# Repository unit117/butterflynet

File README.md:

# KiCad Agent Pipeline

> A multi-agent workflow that operates KiCad end to end: research a physical product, review and normalize the spec, generate the board, repair design-rule failures, and export fabrication files.

This project was built for the GOSIM Paris 2026 Agentic AI Hackathon. The target is a recreation-inspired PCB for Ingo Maurer's **My New Flame** lamp: a tall, narrow 430x30mm board with two LED faces, a stem/base interface, and manufacturable KiCad outputs.

The key idea is not "LLM writes a PCB once." The system keeps an auditable chain of agents around KiCad: source-gathering, claim review, spec branching, deterministic board generation, DRC repair, and fabrication export. The demo UI replays the real agent logs and KiCad artifacts so judges can see where agents made decisions, caught mistakes, and recovered from failed fixes.

---

## Why This Matters

Hardware design is a good stress test for agentic AI because plausible text is not enough. A wrong charger IC, incorrect LED topology, or broken clearance rule becomes a real manufacturing problem. This project shows agents doing the work around the artifact:

- reading source material before creating a spec
- rejecting unsupported or electrically invalid claims
- refusing to build a blocked faithful reconstruction
- branching to a buildable modernized target
- generating KiCad schematic/PCB files
- running automated DRC loops until the board reaches zero violations
- exporting Gerbers, drill files, BOM, placement CSV, and a 3D model

The result is a working local demo plus a complete KiCad hardware project that reviewers can inspect directly.

---

## Demo Flow

Run the local replay UI and press **Play**. The app shows six screens: an overview, then the five pipeline phases.

| Phase | What reviewers see | Why it matters |
|---|---|---|
| 0. Overview | KiCad context and project goal | Frames the real EDA environment, not just a mock UI |
| 1. Research | Sources, facts, unresolved questions, source previews, terminal log | Shows source discipline before design work starts |
| 2. Design | Multi-agent review, rejected claims, branch selection | Shows self-correction and refusal to guess |
| 3. Build | KiCad component groups and generated board structure | Shows the system moving from spec to concrete PCB artifacts |
| 4. Validate | DRC loop, improvements, regressions, reverts, final zero-violation state | Shows agents reading tool feedback and recovering from failures |
| 5. Export | Fabrication bundle, individual files, spinning GLB board preview | Shows manufacturing-ready outputs |

The required 3-5 minute demo video is supplied through the hackathon submission. This repository contains the local demo used to produce that video.

---

## Judging Criteria Fit

**Innovation:** The project treats KiCad as an agent-operable engineering environment. Agents do not only draft text; they inspect evidence, branch specs, run tools, measure failures, and decide when not to proceed.

**Technical depth:** The repo includes a real KiCad 10 project, replay logs, a React/Vite provenance UI, custom KiCad automation scripts, DRC recovery outputs, fabrication files, and a 3D GLB preview.

**Completeness:** The demo covers the whole path from research to export. The hardware project includes `.kicad_pro`, `.kicad_sch`, `.kicad_pcb`, custom footprints, Gerbers, drill files, BOM, position CSV, PDFs, STEP/GLB, and DRC reports.

**Practicality:** The workflow targets a real engineering failure mode: AI systems that hallucinate hardware details and stop before validation. This pipeline makes uncertainty visible and closes the loop with KiCad checks.

**Presentation:** The UI is a deterministic replay of the pipeline, with phase-by-phase controls and visual artifacts for judges to follow in a 3 minute live demo.

---

## Agentic Moments

**Phase 2: self-correction**

- A reviewer agent rejects the proposed MCP73871 charger IC because it is a single-cell Li-Ion charger, while the original target uses 4x AA NiMH cells.
- A design-research agent corrects the claim that the LEDs are physically flame-shaped. Source evidence shows an 8x16 rectangular LED field per face; the flame is rendered by animation.
- The system refuses to build the faithful reconstruction while charger topology remains unresolved, then selects the `v5_modernized` branch as the build target.

**Phase 4: failure recovery**

- DRC starts at 451 violations and reaches 0 after 33 iterations.
- Some proposed fixes improve the board and are kept.
- Some fixes make the DRC count worse and are reverted.
- Later fixes can succeed after earlier routing context changes, showing that the validation loop is state-aware rather than a static checklist.

---

## Run Locally

Requirements:

- Node.js 20+
- npm
- A modern browser

Start the demo:

```bash
cd kicad-agent-ui/frontend
npm install
npm run dev
```

Open:

```text
http://localhost:5173/
```

Build the frontend:

```bash
cd kicad-agent-ui/frontend
npm run build
```

The frontend is self-contained for demo playback. KiCad is not required to run the replay UI, but the hardware files can be opened in KiCad 10 for inspection.

---

## Repository Map

```text
.
├── agents/                         # Agent role prompts and responsibilities
├── examples/                       # Example user prompts for faithful and modernized builds
├── hardware/
│   ├── README.md                   # Hardware artifact notes
│   ├── candle-git-history.bundle   # Preserved original candle project history
│   └── candle/                     # Full KiCad project and generated outputs
├── kicad-agent-ui/
│   ├── backend/                    # FastAPI skeleton for project/pipeline/viewer APIs
│   └── frontend/                   # React/Vite replay UI
├── replays/                        # Canonical NDJSON phase replay logs
├── DEMO.md                         # Demo/provenance notes
├── DISCLOSURE.md                   # Pre-existing vs hackathon-built disclosure
├── SUBMISSION.md                   # Hackathon metadata checklist
└── README.md
```

---

## Hardware Artifacts

The complete KiCad project is in [hardware/candle](hardware/candle).

Key source files:

- [hardware/candle/candle.kicad_pro](hardware/candle/candle.kicad_pro)
- [hardware/candle/candle.kicad_sch](hardware/candle/candle.kicad_sch)
- [hardware/candle/candle.kicad_pcb](hardware/candle/candle.kicad_pcb)
- [hardware/candle/candle.pretty](hardware/candle/candle.pretty)
- [hardware/candle/tools/generate_candle.py](hardware/candle/tools/generate_candle.py)
- [hardware/candle/tools/candle_recovery.py](hardware/candle/tools/candle_recovery.py)
- [hardware/candle/outputs/fabrication](hardware/candle/outputs/fabrication)
- [hardware/candle/outputs/candle.glb](hardware/candle/outputs/candle.glb)

The frontend also serves compact demo copies from:

- [kicad-agent-ui/frontend/public/replays](kicad-agent-ui/frontend/public/replays)
- [kicad-agent-ui/frontend/public/exports/candle](kicad-agent-ui/frontend/public/exports/candle)

Fabrication outputs include:

- front/back copper Gerbers
- two internal copper layers
- solder mask and silkscreen
- edge cuts
- plated and non-plated drill files
- assembly BOM
- position CSV
- fabrication ZIP
- GLB 3D model

---

## Architecture

[Open the architecture diagram](docs/architecture-diagram.svg).

[PNG version](docs/architecture-diagram.png).

```text
User goal
   |
   v
Research agent
   |-- sources consulted
   |-- tagged fact ledger
   |-- unresolved questions
   v
Design review agents
   |-- spec normalizer
   |-- electrical reviewer
   |-- design researcher
   |-- critic
   v
Build agents
   |-- schematic architect
   |-- spec-to-schematic
   |-- placement planner
   |-- route strategist
   v
KiCad automation
   |-- generate_candle.py
   |-- kicad-cli
   |-- canonicalize/stabilize tools
   v
Validation agents
   |-- run DRC
   |-- inspect violations
   |-- patch board
   |-- measure delta
   |-- revert or keep
   v
Export agent
   |-- Gerbers
   |-- drills
   |-- BOM / position CSV
   |-- GLB / STEP
```

---

## Technology

- **EDA:** KiCad 10.0, `kicad-cli`
- **Automation:** Python 3.9 scripts for generation, canonicalization, rendering, DRC experiments, and recovery
- **Frontend:** React 19, TypeScript, Vite
- **Backend:** FastAPI skeleton for project, pipeline, and viewer routes
- **Demo data:** NDJSON replay logs and static KiCad export artifacts
- **Target board:** 430x30mm 4-layer PCB, 256 LEDs, ATtiny1616, 2x IS31FL3731-QF, custom footprints

---

## Pre-Existing vs Hackathon Work

| Pre-existing / carried in | Built or assembled for the hackathon submission |
|---|---|
| Original candle KiCad project and generator history | Public repo structure and preserved hardware bundle |
| Research/spec session artifacts | Five-phase replay model and demo UI |
| DRC reduction history | Validation visualization and provenance narrative |
| KiCad CLI/tooling experiments | Submission-focused docs, phase script, and export preview |

Full disclosure is in [DISCLOSURE.md](DISCLOSURE.md).

---

## Verification

Reviewers can verify the work through:

- [replays](replays): phase-by-phase replay logs
- [hardware/candle/outputs/recovery](hardware/candle/outputs/recovery): DRC recovery reports and summaries
- [hardware/candle/outputs/fabrication](hardware/candle/outputs/fabrication): manufacturing outputs
- [hardware/candle/outputs/docs](hardware/candle/outputs/docs): exported schematic and board PDFs
- [hardware/candle-git-history.bundle](hardware/candle-git-history.bundle): original project history bundle
- [DEMO.md](DEMO.md): demo/provenance notes
- [DISCLOSURE.md](DISCLOSURE.md): scope and provenance disclosure

---

## License

[MIT](LICENSE)

---

*GOSIM Paris 2026 — Agentic AI Hackathon*

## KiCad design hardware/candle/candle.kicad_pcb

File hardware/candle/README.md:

# Candle

This folder contains the KiCad candle hardware artifact for the agent pipeline
demo. The design target is the `v5 modernized` direction described in
[`candle_spec_v5_modernized.md`](./candle_spec_v5_modernized.md): a tall,
exposed LED stem inspired by the My New Flame lamp, with the battery and charge
electronics kept in a concealed base.

This is an auditable generated hardware snapshot, not a hand-polished consumer
product release. It includes the KiCad source project, local footprints,
generated docs, fabrication-format outputs, 3D assets, validation reports, and
the automation scripts used to regenerate or inspect the board.

## Reviewer quick start

- Open `candle.kicad_pro` in KiCad to inspect the schematic and PCB.
- Read `outputs/docs/candle-schematic.pdf` for the electrical architecture.
- Read `outputs/docs/candle-board-front.pdf` and
  `outputs/docs/candle-board-back.pdf` for board plots.
- Inspect `outputs/candle.glb` or `outputs/candle.step` for the 3D board model.
- Inspect `outputs/fabrication/candle-fabrication-bundle.zip` for the exported
  Gerbers, drill files, BOM, placement CSV, and netlist.
- Check `outputs/candle-drc.json`, `outputs/candle-erc.json`, and
  `outputs/recovery/latest-report.md` for validation state and recovery history.

## Status and caveats

The demo UI shows the full agent pipeline, including a validation replay where
agents iterate DRC fixes down to a clean board. This directory preserves the
checked-in KiCad project snapshot and its generated export artifacts for review.
That snapshot is useful for inspecting the real board structure and automation
outputs, but it still has known validation issues listed below.

Do not send this board directly to fabrication as a production design without
resolving the current ERC/DRC items and doing an electrical engineering review.
The fabrication files are included to demonstrate the exporter and the expected
manufacturing artifact shape.

## Active design assets

- `candle.kicad_sch`: architecture schematic for the base power path plus stem
  control/driver partition
- `candle.kicad_pcb`: generated `430 x 30 mm` stem board
- `candle.kicad_pro`: lightweight KiCad project file written by the generator
- `candle.pretty/`: local footprints for the blind-socket stem pads, compact
  matrix LEDs, and exposed service pads
- `tools/generate_candle.py`: repeatable schematic + PCB generator
- `tools/canonicalize_pcb.py`: deterministic `.kicad_pcb` canonicalizer for
  stable UUIDs and section ordering
- `tools/stabilize_candle.py`: optional repeated-run sampler kept for audit and
  comparison work
- `tools/export_candle.py`: repeatable docs/fabrication export helper
- `tools/candle_recovery.py`: harness-driven PCB recovery wrapper that captures
  DRC snapshots, diffs, and crossing hotspots per iteration
- `tools/drc_hotspots.py`: read-only DRC hotspot analyzer grouped by type, net
  pair, and coarse board region

## Exported artifacts

- `outputs/docs/`: schematic and board PDFs for quick review without opening
  KiCad
- `outputs/fabrication/gerbers/`: copper, mask, silkscreen, outline, and job
  files
- `outputs/fabrication/drill/`: plated, non-plated, and internal-layer drill
  files plus drill maps
- `outputs/fabrication/candle-assembly-bom.csv`: generated assembly BOM
- `outputs/fabrication/candle-pos.csv`: generated pick-and-place positions
- `outputs/fabrication/candle-assembly-notes.md`: assembly notes and exclusions
- `outputs/fabrication/candle-fabrication-bundle.zip`: bundled manufacturing
  export
- `outputs/candle.glb` and `outputs/candle.step`: 3D board assets

## Architecture captured here

- Exposed stem PCB sized to the published `430 x 30 mm` envelope
- Dual flame fields with `8 x 16` warm-white LEDs per face
- Stem MCU plus one matrix driver per face
- `4` duplicated bottom power contacts for the concealed base socket
- Base-side `USB-C -> charger/power-path -> battery -> switch -> stem` flow in
  the schematic

## Regeneration

Quick iteration:

```bash
PYTHONPATH="/Applications/KiCad/KiCad.app/Contents/Frameworks/python/site-packages" \
/Applications/KiCad/KiCad.app/Contents/Frameworks/Python.framework/Versions/3.9/bin/python3 \
  tools/generate_candle.py
```

`generate_candle.py` now canonicalizes the saved `.kicad_pcb` before DRC, so a
fresh run produces one stable board file. The current source also reproduced
the same board hash and the same `266`-DRC result across `3/3` repeated
stability runs.

Optional repeated-run sampling:

```bash
PYTHONPATH="/Applications/KiCad/KiCad.app/Contents/Frameworks/python/site-packages" \
/Applications/KiCad/KiCad.app/Contents/Frameworks/Python.framework/Versions/3.9/bin/python3 \
  tools/stabilize_candle.py --runs 8
```

## Export package

```bash
python3 tools/export_candle.py
```

`export_candle.py` now uses the deterministic single-run generator by default.
Use `--stabilize-runs N` only when you explicitly want sampling, or
`--skip-generate` to export the current board as-is. The exporter snapshots the
schematic and PCB into a temp directory before calling `kicad-cli`, which keeps
PDF/netlist generation stable even while the project is being regenerated.

DRC hotspot analysis:

```bash
python3 tools/drc_hotspots.py --top-groups 20
```

The analyzer reads `outputs/candle-drc.json` by default and prints stable
hotspot rollups that are useful for routing recovery and cleanup passes.

Harness-driven recovery snapshot:

```bash
python3 tools/candle_recovery.py run --label working --skip-generate
python3 tools/candle_recovery.py set-baseline --label baseline --skip-generate
```

This writes per-run reports under `outputs/recovery/` using the repo's
CLI-Anything KiCad harness for `pcb drc`, DRC diffing, and track-crossing
grouping.

## Current validation state

- Schematic ERC: `91` violations
- PCB DRC: `266` violations
- PCB shorting items: `0`
- PCB unconnected items: `0`
- Board SHA256: `870a1c23718942aeb22cf7f075a202402b04271010dc7a0cb9bf8b06c47dc183`

The current board is a generated first-pass implementation of the modernized
stem with real matrix placement, routing structure, and exported KiCad assets.
The remaining issues are concentrated in dense driver-fanout geometry,
clearance/track-crossing cleanup, and schematic cleanliness rather than missing
project scaffolding. The latest `stabilize_candle.py --runs 3` sample
reproduced the same `266` board in all three runs, which makes the snapshot
stable enough for audit and replay work even though it is not production-clean.

## Reference material

- `refs/source_documents.md`: reconciled external facts and dimension sources
- `refs/provided_reference_render.png`: visual composition reference
- `specs/candle_spec_deviations.md`: intentional deviations from the active
  modernized build path
- `archive/`: archived earlier specs and the superseded proof-of-concept project

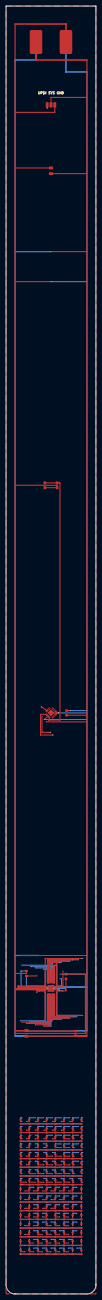
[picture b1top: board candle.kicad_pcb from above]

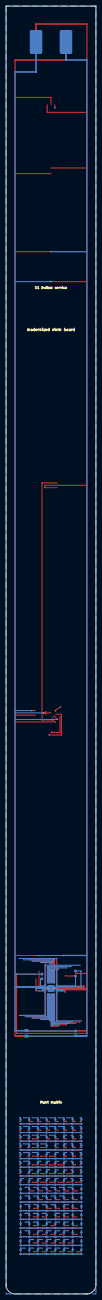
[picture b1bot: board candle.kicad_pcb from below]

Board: 4 copper layers, 30.0 x 430.0 mm, 272 parts (133 on the bottom side), 46 nets.

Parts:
C1, C3, C5: 100n; C_0603_1608Metric
C2, C4: 4.7u; C_0805_2012Metric
C6: 10u; C_0805_2012Metric
C7, C8: 1u; C_0603_1608Metric
D1, D2, D3, D4, D5, D6, D7, D8, D9, D10, D11, D12, D13, D14, D15, D16, D17, D18, D19, D20, D21, D22, D23, D24, D25, D26, D27, D28, D29, D30, D31, D32, D33, D34, D35, D36, D37, D38, D39, D40, D41, D42, D43, D44, D45, D46, D47, D48, D49, D50, D51, D52, D53, D54, D55, D56, D57, D58, D59, D60, D61, D62, D63, D64, D65, D66, D67, D68, D69, D70, D71, D72, D73, D74, D75, D76, D77, D78, D79, D80, D81, D82, D83, D84, D85, D86, D87, D88, D89, D90, D91, D92, D93, D94, D95, D96, D97, D98, D99, D100, D101, D102, D103, D104, D105, D106, D107, D108, D109, D110, D111, D112, D113, D114, D115, D116, D117, D118, D119, D120, D121, D122, D123, D124, D125, D126, D127, D128, D129, D130, D131, D132, D133, D134, D135, D136, D137, D138, D139, D140, D141, D142, D143, D144, D145, D146, D147, D148, D149, D150, D151, D152, D153, D154, D155, D156, D157, D158, D159, D160, D161, D162, D163, D164, D165, D166, D167, D168, D169, D170, D171, D172, D173, D174, D175, D176, D177, D178, D179, D180, D181, D182, D183, D184, D185, D186, D187, D188, D189, D190, D191, D192, D193, D194, D195, D196, D197, D198, D199, D200, D201, D202, D203, D204, D205, D206, D207, D208, D209, D210, D211, D212, D213, D214, D215, D216, D217, D218, D219, D220, D221, D222, D223, D224, D225, D226, D227, D228, D229, D230, D231, D232, D233, D234, D235, D236, D237, D238, D239, D240, D241, D242, D243, D244, D245, D246, D247, D248, D249, D250, D251, D252, D253, D254, D255, D256: WW_2700K; Candle_LED_0603_Matrix
J1: STEM_SOCKET; Candle_StemSocket_4Pad
J2: UPDI_PADS; Candle_ServicePads_1x3
R1, R2: 20k; R_0603_1608Metric
SW1: PCB_BUTTON; SW_Push_1P1T_NO_CK_KMR2
U1: ATtiny1616-M; VQFN-20-1EP_3x3mm_P0.4mm_EP1.7x1.7mm
U2, U3: IS31FL3731-QF; QFN-28-1EP_4x4mm_P0.4mm_EP2.3x2.3mm

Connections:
BTN: SW1.1, U1.5
F_CA1: D1.1, D2.1, D3.1, D4.1, D5.1, D6.1, D7.1, D8.1, D9.2, D17.2, D25.2, D33.2, D41.2, D49.2, D57.2, U2.21
F_CA2: D1.2, D9.1, D10.1, D11.1, D12.1, D13.1, D14.1, D15.1, D16.1, D18.2, D26.2, D34.2, D42.2, D50.2, D58.2, U2.22
F_CA3: D2.2, D10.2, D17.1, D18.1, D19.1, D20.1, D21.1, D22.1, D23.1, D24.1, D27.2, D35.2, D43.2, D51.2, D59.2, U2.23
F_CA4: D3.2, D11.2, D19.2, D25.1, D26.1, D27.1, D28.1, D29.1, D30.1, D31.1, D32.1, D36.2, D44.2, D52.2, D60.2, U2.24
F_CA5: D4.2, D12.2, D20.2, D28.2, D33.1, D34.1, D35.1, D36.1, D37.1, D38.1, D39.1, D40.1, D45.2, D53.2, D61.2, U2.25
F_CA6: D5.2, D13.2, D21.2, D29.2, D37.2, D41.1, D42.1, D43.1, D44.1, D45.1, D46.1, D47.1, D48.1, D54.2, D62.2, U2.26
F_CA7: D6.2, D14.2, D22.2, D30.2, D38.2, D46.2, D49.1, D50.1, D51.1, D52.1, D53.1, D54.1, D55.1, D56.1, D63.2, U2.27
F_CA8: D7.2, D15.2, D23.2, D31.2, D39.2, D47.2, D55.2, D57.1, D58.1, D59.1, D60.1, D61.1, D62.1, D63.1, D64.1, U2.28
F_CA9: D8.2, D16.2, D24.2, D32.2, D40.2, D48.2, D56.2, D64.2, U2.1
F_CB1: D65.1, D66.1, D67.1, D68.1, D69.1, D70.1, D71.1, D72.1, D73.2, D81.2, D89.2, D97.2, D105.2, D113.2, D121.2, U2.7
F_CB2: D65.2, D73.1, D74.1, D75.1, D76.1, D77.1, D78.1, D79.1, D80.1, D82.2, D90.2, D98.2, D106.2, D114.2, D122.2, U2.8
F_CB3: D66.2, D74.2, D81.1, D82.1, D83.1, D84.1, D85.1, D86.1, D87.1, D88.1, D91.2, D99.2, D107.2, D115.2, D123.2, U2.9
F_CB4: D67.2, D75.2, D83.2, D89.1, D90.1, D91.1, D92.1, D93.1, D94.1, D95.1, D96.1, D100.2, D108.2, D116.2, D124.2, U2.10
F_CB5: D68.2, D76.2, D84.2, D92.2, D97.1, D98.1, D99.1, D100.1, D101.1, D102.1, D103.1, D104.1, D109.2, D117.2, D125.2, U2.11
F_CB6: D69.2, D77.2, D85.2, D93.2, D101.2, D105.1, D106.1, D107.1, D108.1, D109.1, D110.1, D111.1, D112.1, D118.2, D126.2, U2.12
F_CB7: D70.2, D78.2, D86.2, D94.2, D102.2, D110.2, D113.1, D114.1, D115.1, D116.1, D117.1, D118.1, D119.1, D120.1, D127.2, U2.13
F_CB8: D71.2, D79.2, D87.2, D95.2, D103.2, D111.2, D119.2, D121.1, D122.1, D123.1, D124.1, D125.1, D126.1, D127.1, D128.1, U2.14
F_CB9: D72.2, D80.2, D88.2, D96.2, D104.2, D112.2, D120.2, D128.2, U2.15
GND: C1.2, C2.2, C3.2, C4.2, C5.2, C6.2, C7.2, C8.2, J1.2, J1.4, J2.3, R1.2, R2.2, SW1.2, U1.3, U1.10, U1.11, U1.21, U2.4, U2.5, U2.17, U2.18, U2.29, U3.4, U3.5, U3.17, U3.29
R_CA1: D129.1, D130.1, D131.1, D132.1, D133.1, D134.1, D135.1, D136.1, D144.2, D152.2, D160.2, D168.2, D176.2, D184.2, D192.2, U3.21
R_CA2: D136.2, D137.1, D138.1, D139.1, D140.1, D141.1, D142.1, D143.1, D144.1, D151.2, D159.2, D167.2, D175.2, D183.2, D191.2, U3.22
R_CA3: D135.2, D143.2, D145.1, D146.1, D147.1, D148.1, D149.1, D150.1, D151.1, D152.1, D158.2, D166.2, D174.2, D182.2, D190.2, U3.23
R_CA4: D134.2, D142.2, D150.2, D153.1, D154.1, D155.1, D156.1, D157.1, D158.1, D159.1, D160.1, D165.2, D173.2, D181.2, D189.2, U3.24
R_CA5: D133.2, D141.2, D149.2, D157.2, D161.1, D162.1, D163.1, D164.1, D165.1, D166.1, D167.1, D168.1, D172.2, D180.2, D188.2, U3.25
R_CA6: D132.2, D140.2, D148.2, D156.2, D164.2, D169.1, D170.1, D171.1, D172.1, D173.1, D174.1, D175.1, D176.1, D179.2, D187.2, U3.26
R_CA7: D131.2, D139.2, D147.2, D155.2, D163.2, D171.2, D177.1, D178.1, D179.1, D180.1, D181.1, D182.1, D183.1, D184.1, D186.2, U3.27
R_CA8: D130.2, D138.2, D146.2, D154.2, D162.2, D170.2, D178.2, D185.1, D186.1, D187.1, D188.1, D189.1, D190.1, D191.1, D192.1, U3.28
R_CA9: D129.2, D137.2, D145.2, D153.2, D161.2, D169.2, D177.2, D185.2, U3.1
R_CB1: D193.1, D194.1, D195.1, D196.1, D197.1, D198.1, D199.1, D200.1, D208.2, D216.2, D224.2, D232.2, D240.2, D248.2, D256.2, U3.7
R_CB2: D200.2, D201.1, D202.1, D203.1, D204.1, D205.1, D206.1, D207.1, D208.1, D215.2, D223.2, D231.2, D239.2, D247.2, D255.2, U3.8
R_CB3: D199.2, D207.2, D209.1, D210.1, D211.1, D212.1, D213.1, D214.1, D215.1, D216.1, D222.2, D230.2, D238.2, D246.2, D254.2, U3.9
R_CB4: D198.2, D206.2, D214.2, D217.1, D218.1, D219.1, D220.1, D221.1, D222.1, D223.1, D224.1, D229.2, D237.2, D245.2, D253.2, U3.10
R_CB5: D197.2, D205.2, D213.2, D221.2, D225.1, D226.1, D227.1, D228.1, D229.1, D230.1, D231.1, D232.1, D236.2, D244.2, D252.2, U3.11
R_CB6: D196.2, D204.2, D212.2, D220.2, D228.2, D233.1, D234.1, D235.1, D236.1, D237.1, D238.1, D239.1, D240.1, D243.2, D251.2, U3.12
R_CB7: D195.2, D203.2, D211.2, D219.2, D227.2, D235.2, D241.1, D242.1, D243.1, D244.1, D245.1, D246.1, D247.1, D248.1, D250.2, U3.13
R_CB8: D194.2, D202.2, D210.2, D218.2, D226.2, D234.2, D242.2, D249.1, D250.1, D251.1, D252.1, D253.1, D254.1, D255.1, D256.1, U3.14
R_CB9: D193.2, D201.2, D209.2, D217.2, D225.2, D233.2, D241.2, D249.2, U3.15
SCL: U1.2, U2.20, U3.20
SDA: U1.1, U2.19, U3.19
SYS: C1.1, C2.1, C3.1, C4.1, C5.1, C6.1, J1.1, J1.3, J2.2, U1.4, U2.2, U2.3, U3.2, U3.3, U3.18
U2_CFILT: C7.1, U2.16
U2_REXT: R1.1, U2.6
U3_CFILT: C8.1, U3.16
U3_REXT: R2.1, U3.6
UPDI: J2.1, U1.19, U1.20

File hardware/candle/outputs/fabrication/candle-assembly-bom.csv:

Refs,Value,Footprint,Qty,Notes
D1-D256,WW_2700K,candle:Candle_LED_0603_Matrix,256,"Dual 8x16 flame fields, one matrix per face"
U1,ATtiny1616-M,Package_DFN_QFN:VQFN-20-1EP_3x3mm_P0.4mm_EP1.7x1.7mm,1,Stem MCU
"U2,U3",IS31FL3731-QF,Package_DFN_QFN:QFN-28-1EP_4x4mm_P0.4mm_EP2.3x2.3mm,2,Front and rear charlieplex matrix drivers
SW1,PCB_BUTTON,Button_Switch_SMD:SW_Push_1P1T_NO_CK_KMR2,1,User control button on stem
"C1,C3,C5",100n,Capacitor_SMD:C_0603_1608Metric,3,Local decoupling
"C2,C4",4.7u,Capacitor_SMD:C_0805_2012Metric,2,Bulk bypass on driver power rail
C6,10u,Capacitor_SMD:C_0805_2012Metric,1,Bulk bypass on stem power rail
"C7,C8",1u,Capacitor_SMD:C_0603_1608Metric,2,Driver C_FILT filter caps
"R1,R2",20k,Resistor_SMD:R_0603_1608Metric,2,Driver current-set resistors
J1,STEM_SOCKET,candle:Candle_StemSocket_4Pad,1,"Concealed blind-socket contact geometry; board-integrated, not a purchased part"
J2,UPDI_PADS,candle:Candle_ServicePads_1x3,1,Board-integrated exposed service pads
"UBASE1,JUSB1,BT1,SWBASE1,DBASE1,RCC1,RCC2,RLED1,RTS1,RISET1,RILIM1,RTMR1,CUSB1,CSYS1",Base-side schematic only,Off-board / base assembly,1 set,"Captured in schematic, not laid out on the visible stem PCB"

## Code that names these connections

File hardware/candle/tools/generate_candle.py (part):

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        },
        {"op": "add-wire", "from": {"at": [154.94, 91.44]}, "to": {"ref": "SWBASE1", "pin": "1"}},
        {"op": "add-wire", "from": {"ref": "SWBASE1", "pin": "2"}, "to": {"at": [208.28, 91.44]}},
        {"op": "add-label", "name": "SYS", "at": [208.28, 91.44]},
        {
            "op": "add-symbol",
            "lib_id": "Device:R",
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            "at": [231.14, 91.44],
        },
        {"op": "add-wire", "from": {"ref": "JSTEM1", "pin": "1"}, "to": {"at": [218.44, 99.06]}},
        {"op": "add-label", "name": "SYS", "at": [218.44, 99.06]},
        {"op": "add-wire", "from": {"ref": "JSTEM1", "pin": "2"}, "to": {"at": [218.44, 96.52]}},
        {"op": "add-power", "lib_id": "power:GND", "at": [218.44, 96.52]},
        {"op": "add-wire", "from": {"ref": "JSTEM1", "pin": "3"}, "to": {"at": [218.44, 93.98]}},
        {"op": "add-label", "name": "SYS", "at": [218.44, 93.98]},
        {"op": "add-wire", "from": {"ref": "JSTEM1", "pin": "4"}, "to": {"at": [218.44, 91.44]}},
        {"op": "add-power", "lib_id": "power:GND", "at": [218.44, 91.44]},
        {
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            "at": [330.2, 96.52],
        },
        {"op": "add-wire", "from": {"at": [330.2, 73.66]}, "to": {"at": [330.2, 66.04]}},
        {"op": "add-label", "name": "SYS", "at": [330.2, 66.04]},
        {"op": "add-wire", "from": {"at": [330.2, 119.38]}, "to": {"at": [330.2, 127.0]}},
        {"op": "add-power", "lib_id": "power:GND", "at": [330.2, 127.0]},
        {
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            "at": [355.6, 96.52],
        },
        {"op": "add-wire", "from": {"ref": "C5", "pin": "1"}, "to": {"at": [347.98, 96.52]}},
        {"op": "add-label", "name": "SYS", "at": [347.98, 96.52]},
        {"op": "add-wire", "from": {"ref": "C5", "pin": "2"}, "to": {"at": [363.22, 96.52]}},
        {"op": "add-power", "lib_id": "power:GND", "at": [363.22, 96.52]},
        {
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        {"op": "add-wire", "from": {"ref": "SW1", "pin": "1"}, "to": {"at": [294.64, 142.24]}},
        {"op": "add-power", "lib_id": "power:GND", "at": [294.64, 142.24]},
        {"op": "add-wire", "from": {"ref": "SW1", "pin": "2"}, "to": {"at": [320.04, 142.24]}},
        {"op": "add-label", "name": "BTN", "at": [320.04, 142.24]},
        {"op": "add-wire", "from": {"at": [345.44, 88.9]}, "to": {"at": [350.52, 88.9]}},
        {"op": "add-label", "name": "BTN", "at": [350.52, 88.9]},
        {"op": "add-wire", "from": {"at": [345.44, 83.82]}, "to": {"at": [350.52, 83.82]}},
        {"op": "add-label", "name": "SDA", "at": [350.52, 83.82]},
        {"op": "add-wire", "from": {"at": [345.44, 86.36]}, "to": {"at": [350.52, 86.36]}},
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            "at": [287.02, 93.98],
        },
        {"op": "add-wire", "from": {"ref": "JPROG1", "pin": "1"}, "to": {"at": [274.32, 101.6]}},
        {"op": "add-label", "name": "UPDI", "at": [274.32, 101.6]},
        {"op": "add-wire", "from": {"ref": "JPROG1", "pin": "2"}, "to": {"at": [274.32, 99.06]}},
        {"op": "add-label", "name": "SYS", "at": [274.32, 99.06]},
        {"op": "add-wire", "from": {"ref": "JPROG1", "pin": "3"}, "to": {"at": [274.32, 96.52]}},
        {"op": "add-power", "lib_id": "power:GND", "at": [274.32, 96.52]},
        {"op": "add-wire", "from": {"at": [345.44, 78.74]}, "to": {"at": [350.52, 78.74]}},
        {"op": "add-label", "name": "UPDI", "at": [350.52, 78.74]},
        {
            "op": "add-symbol",
            "lib_id": "Driver_LED:IS31FL3731-QF",
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        sy = 93.98
        xl = sym_x - 12.7 - 7.62
        patches.append({"op": "add-wire", "from": {"ref": ref, "pin": "2"}, "to": {"at": [sym_x, sy - 27.94 - 7.62]}})
        patches.append({"op": "add-label", "name": "SYS", "at": [sym_x, sy - 27.94 - 7.62]})
        patches.append({"op": "add-wire", "from": {"ref": ref, "pin": "3"}, "to": {"at": [xl, sy - 12.7]}})
        patches.append({"op": "add-label", "name": "SYS", "at": [xl, sy - 12.7]})
        patches.append({"op": "add-wire", "from": {"ref": ref, "pin": "5"}, "to": {"at": [sym_x, sy + 27.94 + 7.62]}})
        patches.append({"op": "add-power", "lib_id": "power:GND", "at": [sym_x, sy + 27.94 + 7.62]})
        patches.append({"op": "add-wire", "from": {"ref": ref, "pin": "29"}, "to": {"at": [sym_x + 2.54, sy + 27.94 + 7.62]}})
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            patches.append({"op": "add-power", "lib_id": "power:GND", "at": [xl, sy - 17.78]})
        else:
            patches.append({"op": "add-wire", "from": {"ref": ref, "pin": "18"}, "to": {"at": [xl, sy - 17.78]}})
            patches.append({"op": "add-label", "name": "SYS", "at": [xl, sy - 17.78]})
        patches.append({"op": "add-wire", "from": {"ref": ref, "pin": "19"}, "to": {"at": [xl, sy - 22.86]}})
        patches.append({"op": "add-label", "name": "SDA", "at": [xl, sy - 22.86]})
        patches.append({"op": "add-wire", "from": {"ref": ref, "pin": "20"}, "to": {"at": [xl, sy - 20.32]}})
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                "at": [584.2, 68.58],
            },
            {"op": "add-wire", "from": {"ref": "R1", "pin": "1"}, "to": {"at": [373.38, 68.58]}},
            {"op": "add-label", "name": "U2_REXT", "at": [373.38, 68.58]},
            {"op": "add-wire", "from": {"ref": "R1", "pin": "2"}, "to": {"at": [388.62, 68.58]}},
            {"op": "add-power", "lib_id": "power:GND", "at": [388.62, 68.58]},
            {"op": "add-wire", "from": {"ref": "R2", "pin": "1"}, "to": {"at": [576.58, 68.58]}},
            {"op": "add-label", "name": "U3_REXT", "at": [576.58, 68.58]},
            {"op": "add-wire", "from": {"ref": "R2", "pin": "2"}, "to": {"at": [591.82, 68.58]}},
            {"op": "add-power", "lib_id": "power:GND", "at": [591.82, 68.58]},
            {
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                "at": [599.44, 68.58],
            },
            {"op": "add-wire", "from": {"ref": "C7", "pin": "1"}, "to": {"at": [388.62, 68.58]}},
            {"op": "add-label", "name": "U2_CFILT", "at": [388.62, 68.58]},
            {"op": "add-wire", "from": {"ref": "C7", "pin": "2"}, "to": {"at": [403.86, 68.58]}},
            {"op": "add-power", "lib_id": "power:GND", "at": [403.86, 68.58]},
            {"op": "add-wire", "from": {"ref": "C8", "pin": "1"}, "to": {"at": [591.82, 68.58]}},
            {"op": "add-label", "name": "U3_CFILT", "at": [591.82, 68.58]},
            {"op": "add-wire", "from": {"ref": "C8", "pin": "2"}, "to": {"at": [607.06, 68.58]}},
            {"op": "add-power", "lib_id": "power:GND", "at": [607.06, 68.58]},
            {
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
    for ref, x_left, x_right in (("C1", 373.38, 388.62), ("C2", 389.89, 405.13), ("C3", 576.58, 591.82), ("C4", 593.09, 608.33)):
        patches.append({"op": "add-wire", "from": {"ref": ref, "pin": "1"}, "to": {"at": [x_left, 142.24]}})
        patches.append({"op": "add-label", "name": "SYS", "at": [x_left, 142.24]})
        patches.append({"op": "add-wire", "from": {"ref": ref, "pin": "2"}, "to": {"at": [x_right, 142.24]}})
        patches.append({"op": "add-power", "lib_id": "power:GND", "at": [x_right, 142.24]})

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    sw1_gnd_pads.sort()
    add_track(board, nets["GND"], "F.Cu", sw1_gnd_pads[0], sw1_gnd_pads[-1], 0.18)
    add_manhattan(board, nets["GND"], "F.Cu", sw1_gnd_pads[-1], (FRONT_GND_TRUNK_X, BUTTON_Y_MM), 0.18)
    updi_pin = to_mm(pad(placed["U1"], "19").GetPosition())
    updi_j2 = to_mm(pad(placed["J2"], "1").GetPosition())
    updi_bcu_x = 11.8
    updi_via_top = (updi_j2[0], 34.0)
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    add_via(board, nets["UPDI"], updi_via_top)
    add_manhattan(board, nets["UPDI"], "In2.Cu", updi_via_top, updi_via_bot, 0.18, via_x=updi_bcu_x)
    add_via(board, nets["UPDI"], updi_via_bot)
    add_track(board, nets["UPDI"], "F.Cu", updi_via_bot, updi_pin, 0.18)
    u1_sys = to_mm(pad(placed["U1"], "4").GetPosition())
    u1_sys_escape = (13.4, 239.0)
    add_via(board, nets["SYS"], u1_sys, drill_mm=0.075, diameter_mm=0.175,
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
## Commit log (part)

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2026-04-13 Add GOSIM hackathon rules and theme notes
2026-05-06 Tighten demo script overview
2026-05-06 Prepare public hackathon submission
2026-05-06 Polish demo phase previews
2026-05-06 Ignore hackathon info files
2026-05-06 Improve submission README
2026-05-06 Add demo video
2026-05-06 Improve demo artifact progression UI
2026-05-06 Add architecture diagram
2026-05-06 Simplify architecture diagram
2026-05-06 Rename architecture diagram title
2026-05-06 Add PNG architecture diagram
2026-05-06 Update demo video
